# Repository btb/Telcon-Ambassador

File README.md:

# Telcon Ambassador Portable Terminals

The Telcon Ambassador was a series of portable terminals by Telcon Industries (who later created the Zorba portable computer).

The info here is primarily derived from my reverse-engineering of a Telcon Ambassador IV which I acquired in very rough shape.

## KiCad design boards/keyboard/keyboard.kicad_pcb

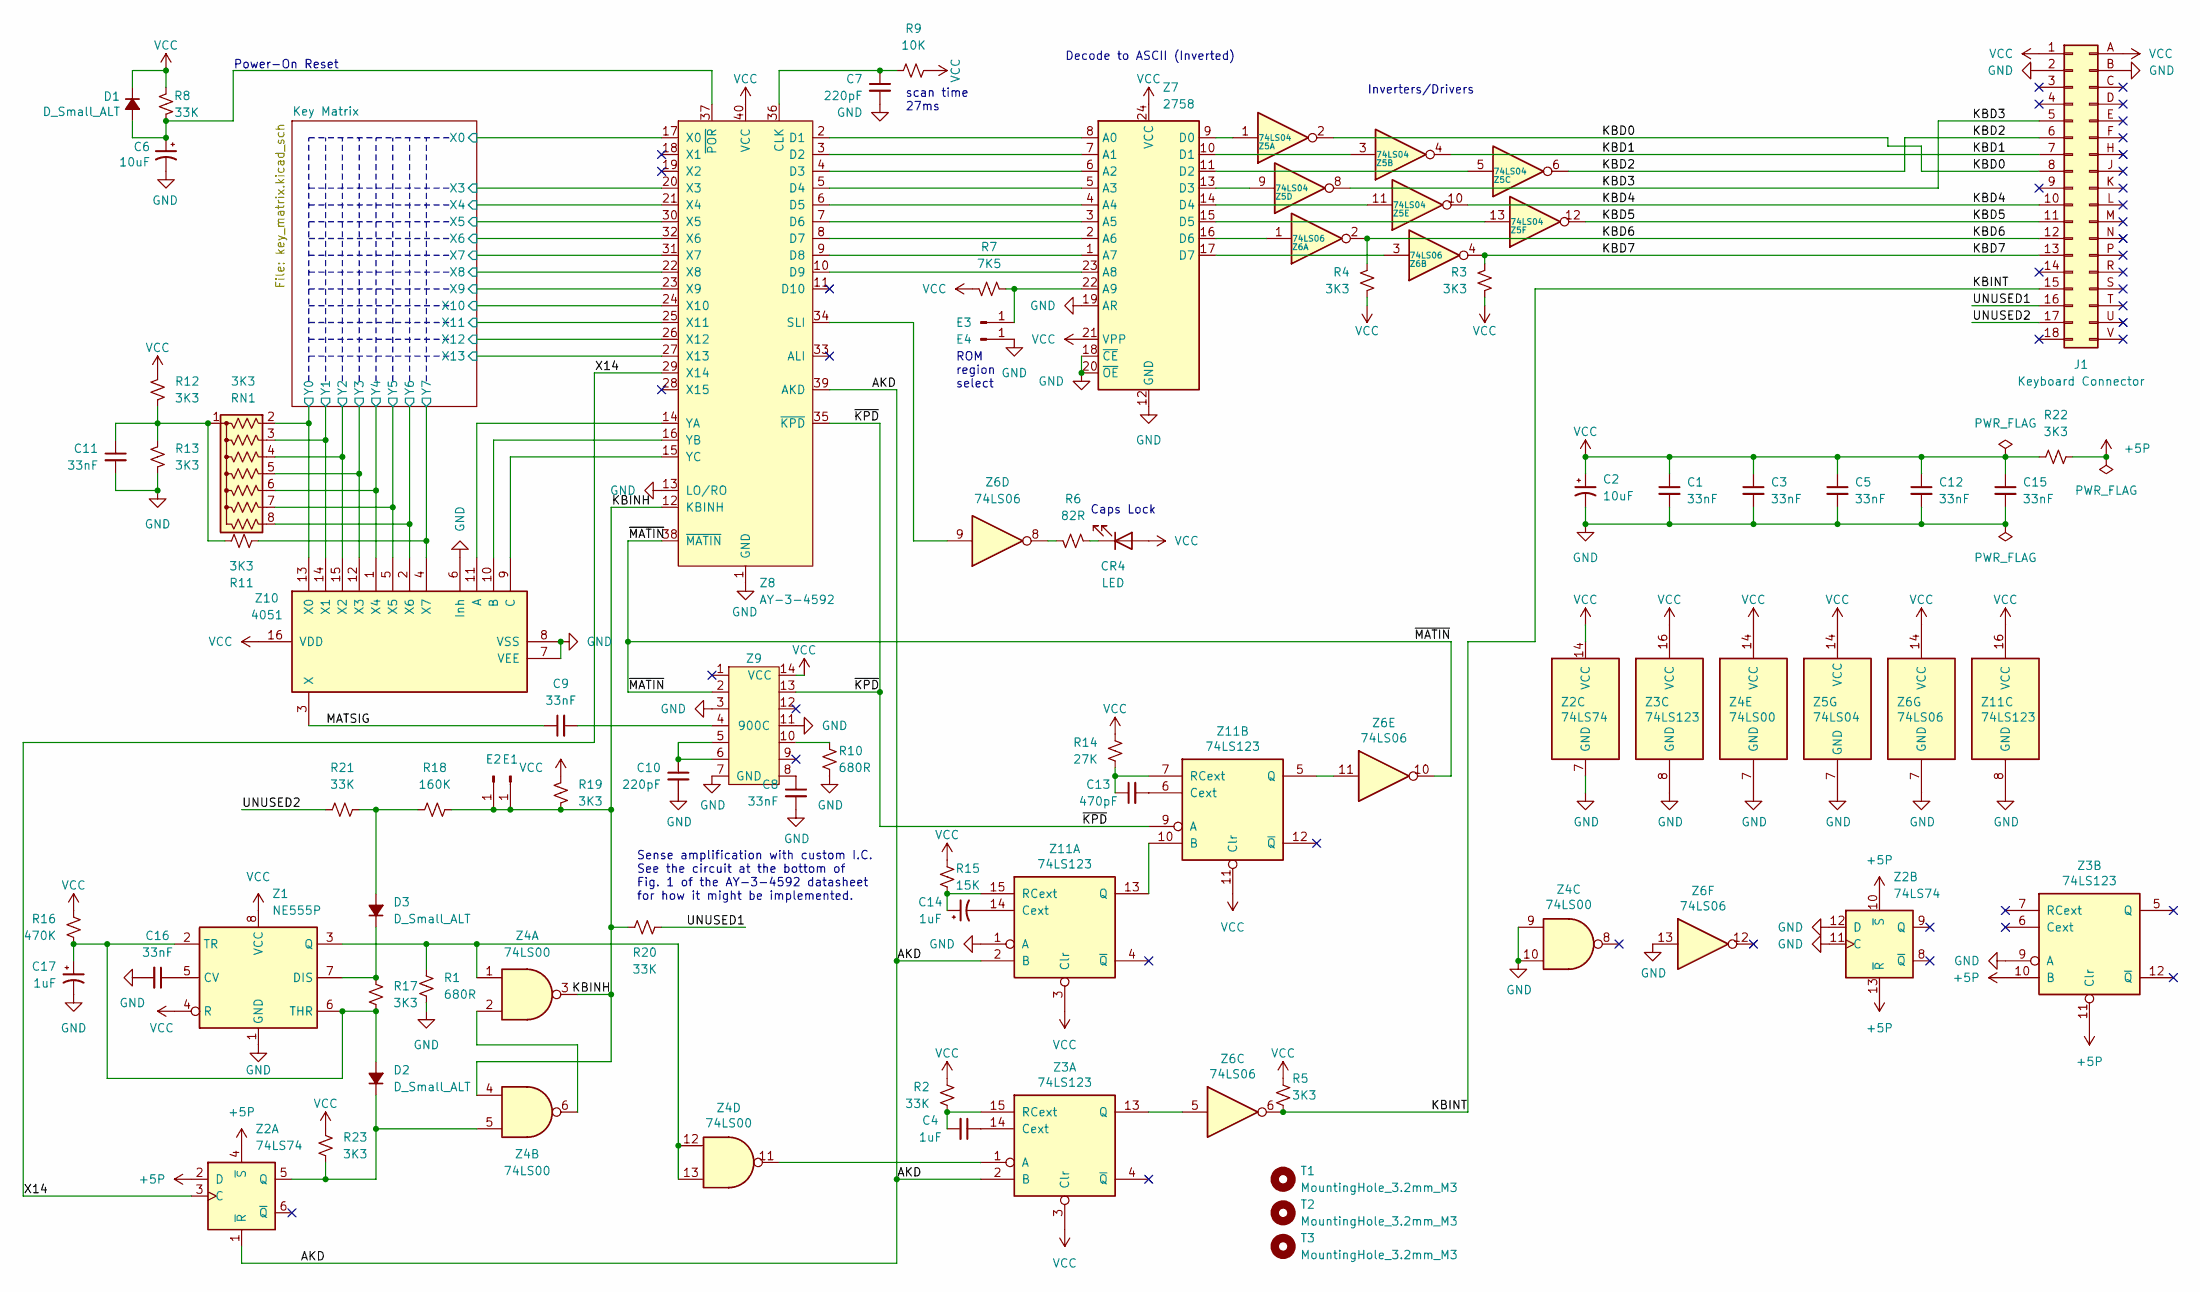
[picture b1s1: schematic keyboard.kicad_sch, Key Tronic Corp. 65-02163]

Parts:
C1, C3, C5, C8, C9, C11, C12, C15, C16: 33nF; C_Axial_L3.8mm_D2.6mm_P12.7mm_Horizontal
C2: 10uF; CP_Radial_D8.0mm_P3.80mm
C4: 1uF; C_Rect_L7.0mm_W2.5mm_P5.00mm
C6: 10uF; CP_Radial_D8.0mm_P3.50mm
C7, C10: 220pF; C_Disc_D6.0mm_W2.5mm_P6.35mm
C13: 470pF; C_Axial_L3.8mm_D2.6mm_P12.7mm_Horizontal
C14: 1uF; CP_Axial_L11.0mm_D5.0mm_P18.00mm_Horizontal
C17: 1uF; CP_Axial_L9.0mm_D3.5mm_P12.7mm_Horizontal
CR4: LED; LED_D5.0mm
D1, D2, D3: D_Small_ALT; D_T-1_P12.70mm_Horizontal
E1, E2: Conn_01x01_Male; PinHeader_1x01_P2.54mm_Vertical
E3: A9; PinHeader_1x01_P2.54mm_Vertical
E4: GND; PinHeader_1x01_P2.54mm_Vertical
J1: Keyboard Connector; CARDEDGE_2x18_P3.96mm
R1, R10: 680R; R_Axial_DIN0309_L9.0mm_D3.2mm_P12.70mm_Horizontal
R2, R8, R20, R21: 33K; R_Axial_DIN0309_L9.0mm_D3.2mm_P12.70mm_Horizontal
R3, R4, R5, R11, R12, R13, R17, R19, R22, R23: 3K3; R_Axial_DIN0309_L9.0mm_D3.2mm_P12.70mm_Horizontal
R6: 82R; R_Axial_DIN0309_L9.0mm_D3.2mm_P12.70mm_Horizontal
R7: 7K5; R_Axial_DIN0309_L9.0mm_D3.2mm_P12.70mm_Horizontal
R9: 10K; R_Axial_DIN0309_L9.0mm_D3.2mm_P12.70mm_Horizontal
R14: 27K; R_Axial_DIN0309_L9.0mm_D3.2mm_P12.70mm_Horizontal
R15: 15K; R_Axial_DIN0309_L9.0mm_D3.2mm_P12.70mm_Horizontal
R16: 470K; R_Axial_DIN0309_L9.0mm_D3.2mm_P12.70mm_Horizontal
R18: 160K; R_Axial_DIN0309_L9.0mm_D3.2mm_P12.70mm_Horizontal
RN1: 3K3; R_Array_SIP8
T1, T2, T3: MountingHole_3.2mm_M3
Z1: NE555P; DIP-8_W7.62mm
Z2: 74LS74; DIP-14_W7.62mm
Z3, Z11: 74LS123; DIP-16_W7.62mm
Z4: 74LS00; DIP-14_W7.62mm
Z5: 74LS04; DIP-14_W7.62mm
Z6: 74LS06; DIP-14_W7.62mm
Z7: 2758; DIP-24_W15.24mm
Z8: AY-3-4592; DIP-40_W15.24mm_Socket
Z9: 900C; DIP-14_W7.62mm
Z10: 4051; DIP-16_W7.62mm

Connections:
+5P: R22.2, Z2.2 (D), Z2.4 (~S), Z2.10 (~S), Z2.13 (~R), Z3.10 (B), Z3.11 (Clr)
/AKD: Z2.1 (~R), Z3.2 (B), Z8.39 (AKD), Z11.2 (B)
/KBD0: J1.8, Z5.2
/KBD1: J1.7, Z5.4
/KBD2: J1.6, Z5.6
/KBD3: J1.5, Z5.8
/KBD4: J1.10, Z5.10
/KBD5: J1.11, Z5.12
/KBD6: J1.12, R4.2, Z6.2
/KBD7: J1.13, R3.2, Z6.4
/KBINH: E1.1, E2.1, R18.2, R19.2, R20.1, Z4.3, Z4.4, Z8.12 (KBINH)
/KBINT: J1.15, R5.2, Z6.6
/Key Matrix/X0: Z8.17 (X0); also elsewhere on the board
/Key Matrix/X3: Z8.20 (X3); also elsewhere on the board
/Key Matrix/X4: Z8.21 (X4); also elsewhere on the board
/Key Matrix/X5: Z8.30 (X5); also elsewhere on the board
/Key Matrix/X6: Z8.32 (X6); also elsewhere on the board
/Key Matrix/X7: Z8.31 (X7); also elsewhere on the board
/Key Matrix/X8: Z8.22 (X8); also elsewhere on the board
/Key Matrix/X9: Z8.23 (X9); also elsewhere on the board
/Key Matrix/X10: Z8.24 (X10); also elsewhere on the board
/Key Matrix/X11: Z8.25 (X11); also elsewhere on the board
/Key Matrix/X12: Z8.26 (X12); also elsewhere on the board
/Key Matrix/X13: Z8.27 (X13); also elsewhere on the board
/Key Matrix/Y0: RN1.2 (R1), Z10.13 (X0); also elsewhere on the board
/Key Matrix/Y1: RN1.3 (R2), Z10.14 (X1); also elsewhere on the board
/Key Matrix/Y2: RN1.4 (R3), Z10.15 (X2); also elsewhere on the board
/Key Matrix/Y3: RN1.5 (R4), Z10.12 (X3); also elsewhere on the board
/Key Matrix/Y4: RN1.6 (R5), Z10.1 (X4); also elsewhere on the board
/Key Matrix/Y5: RN1.7 (R6), Z10.5 (X5); also elsewhere on the board
/Key Matrix/Y6: RN1.8 (R7), Z10.2 (X6); also elsewhere on the board
/Key Matrix/Y7: R11.2, Z10.4 (X7); also elsewhere on the board
/MATSIG: C9.1, Z10.3 (X)
/UNUSED1: J1.16, R20.2
/UNUSED2: J1.17, R21.2
/X14: Z2.3 (C), Z8.29 (X14)
/~KPD: Z8.35 (~KPD), Z9.13, Z11.9 (A)
/~MATIN: Z6.10, Z8.38 (~MATIN), Z9.2
GND: C1.2, C2.2, C3.2, C5.2, C6.2, C7.2, C8.2, C10.2, C11.2, C12.2, C15.2, C16.2, C17.2, E4.1, J1.2, J1.B, R1.2, R10.2, R13.2, Z1.1 (GND), Z2.7 (GND), Z2.11 (C), Z2.12 (D), Z3.8 (GND), Z3.9 (A), Z4.7 (GND), Z4.9, Z4.10, Z5.7 (GND), Z6.7 (GND), Z6.13, Z7.12 (GND), Z7.18 (~CE), Z7.19 (AR), Z7.20 (~OE), Z8.1 (GND), Z8.13 (LO/RO), Z9.3, Z9.7 (GND), Z9.11, Z10.6 (Inh), Z10.7 (VEE), Z10.8 (VSS), Z11.1 (A), Z11.8 (GND); also elsewhere on the board
unnamed: C4.1, Z3.14 (Cext)
unnamed: C4.2, R2.2, Z3.15 (RCext)
unnamed: C6.1, D1.2 (A), R8.2, Z8.37 (~POR)
unnamed: C7.1, R9.2, Z8.36 (CLK)
unnamed: C8.1, Z9.8
unnamed: C9.2, Z9.4
unnamed: C10.1, Z9.5, Z9.6
unnamed: C11.1, R11.1, R12.2, R13.1, RN1.1 (common)
unnamed: C13.1, R14.2, Z11.7 (RCext)
unnamed: C13.2, Z11.6 (Cext)
unnamed: C14.1, R15.2, Z11.15 (RCext)
unnamed: C14.2, Z11.14 (Cext)
unnamed: C16.1, Z1.5 (CV)
unnamed: C17.1, D2.2 (A), R16.2, R17.2, Z1.2 (TR), Z1.6 (THR)
unnamed: CR4.1 (K), R6.1
unnamed: D2.1 (K), R23.2, Z2.5 (Q), Z4.5
unnamed: D3.1 (K), R17.1, Z1.7 (DIS)
unnamed: D3.2 (A), R18.1, R21.1
unnamed: E3.1, R7.2, Z7.22 (A9)
unnamed: R1.1, Z1.3 (Q), Z4.1, Z4.12, Z4.13
unnamed: R6.2, Z6.8
unnamed: R10.1, Z9.10
unnamed: Z3.1 (A), Z4.11
unnamed: Z3.13 (Q), Z6.5
unnamed: Z4.2, Z4.6
unnamed: Z5.1, Z7.9 (D0)
unnamed: Z5.3, Z7.10 (D1)
unnamed: Z5.5, Z7.11 (D2)
unnamed: Z5.9, Z7.13 (D3)
unnamed: Z5.11, Z7.14 (D4)
unnamed: Z5.13, Z7.15 (D5)
unnamed: Z6.1, Z7.16 (D6)
unnamed: Z6.3, Z7.17 (D7)
unnamed: Z6.9, Z8.34 (SLI)
unnamed: Z7.1 (A7), Z8.9 (D8)
unnamed: Z7.2 (A6), Z8.8 (D7)
unnamed: Z7.3 (A5), Z8.7 (D6)
unnamed: Z7.4 (A4), Z8.6 (D5)
unnamed: Z7.5 (A3), Z8.5 (D4)
unnamed: Z7.6 (A2), Z8.4 (D3)
unnamed: Z7.7 (A1), Z8.3 (D2)
unnamed: Z7.8 (A0), Z8.2 (D1)
unnamed: Z7.23 (A8), Z8.10 (D9)
unnamed: Z8.15 (YC), Z10.9 (C)
unnamed: Z8.16 (YB), Z10.10 (B)
unnamed: Z8.14 (YA), Z10.11 (A)
unnamed: Z6.11, Z11.5 (Q)
unnamed: Z11.10 (B), Z11.13 (Q)
VCC: C1.1, C2.1, C3.1, C5.1, C12.1, C15.1, CR4.2 (A), D1.1 (K), J1.1, J1.A, R2.1, R3.1, R4.1, R5.1, R7.1, R8.1, R9.1, R12.1, R14.1, R15.1, R16.1, R19.1, R22.1, R23.1, Z1.4 (R), Z1.8 (VCC), Z2.14 (VCC), Z3.3 (Clr), Z3.16 (VCC), Z4.14 (VCC), Z5.14 (VCC), Z6.14 (VCC), Z7.21 (VPP), Z7.24 (VCC), Z8.40 (VCC), Z9.14 (VCC), Z10.16 (VDD), Z11.3 (Clr), Z11.11 (Clr), Z11.16 (VCC)

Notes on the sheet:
Sense amplification with custom I.C. See the circuit at the bottom of Fig. 1 of the AY-3-4592 datasheet for how it might be implemented.
ROM region select
Caps Lock
Power-On Reset
Inverters/Drivers
Decode to ASCII (Inverted)
scan time 27ms

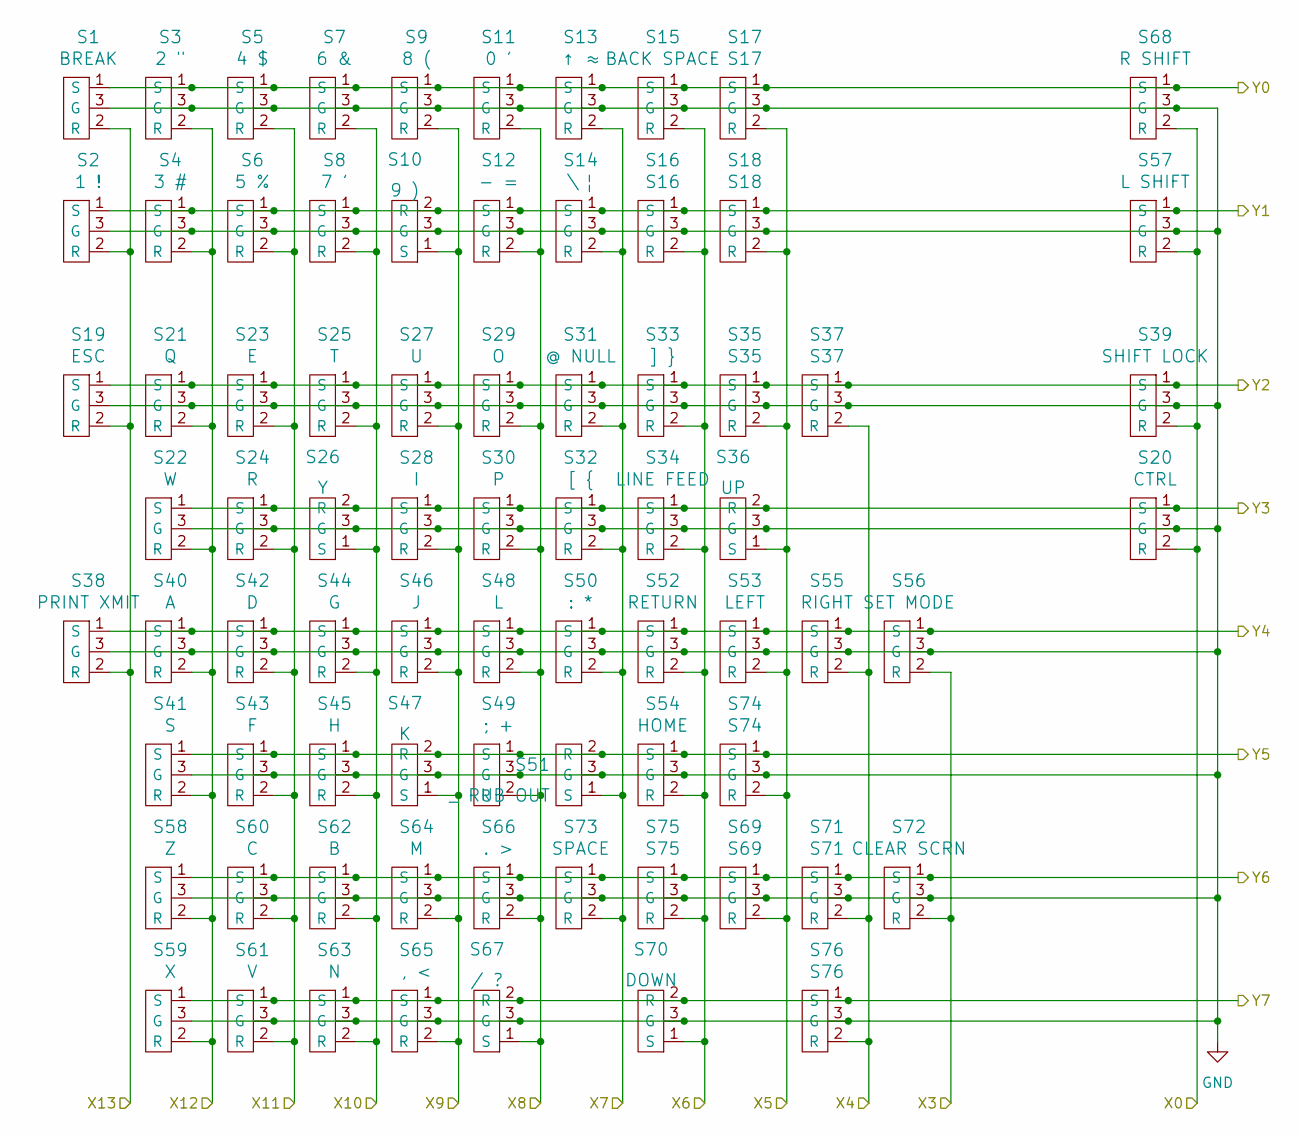
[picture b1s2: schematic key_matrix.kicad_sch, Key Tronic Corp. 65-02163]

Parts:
S1: BREAK; KTCPadScrew
S2: 1 !; KTCPad
S3: 2 "; KTCPad
S4: 3 #; KTCPad
S5: 4 $; KTCPadScrew
S6: 5 %; KTCPad
S7: 6 &; KTCPad
S8: 7 ’; KTCPad
S9: 8 (; KTCPad
S10: 9 ); KTCPadScrew
S11: 0 '; KTCPad
S12: - =; KTCPad
S13: ↑ ≈; KTCPad
S14: \ ¦; KTCPad
S15: BACK SPACE; KTCPadScrew
S16: S16; KTCPad
S17: S17; KTCPad
S18: S18; KTCPad
S19: ESC; KTCPad
S20: CTRL; KTCPad
S21: Q; KTCPadScrew
S22: W; KTCPad
S23: E; KTCPad
S24: R; KTCPad
S25: T; KTCPad
S26: Y; KTCPadScrew
S27: U; KTCPad
S28: I; KTCPad
S29: O; KTCPad
S30: P; KTCPad
S31: @ NULL; KTCPadScrew
S32: [ {; KTCPad
S33: ] }; KTCPad
S34: LINE FEED; KTCPad
S35: S35; KTCPad
S36: UP; KTCPadScrew
S37: S37; KTCPad
S38: PRINT XMIT; KTCPadScrew
S39: SHIFT LOCK; KTCPad
S40: A; KTCPad
S41: S; KTCPad
S42: D; KTCPadScrew
S43: F; KTCPad
S44: G; KTCPad
S45: H; KTCPad
S46: J; KTCPad
S47: K; KTCPadScrew
S48: L; KTCPad
S49: ; +; KTCPad
S50: : *; KTCPad
S51: _ RUB OUT; KTCPadScrew
S52: RETURN; KTCPad
S53: LEFT; KTCPadScrew
S54: HOME; KTCPad
S55: RIGHT; KTCPadScrew
S56: SET MODE; KTCPad
S57: L SHIFT; KTCPadScrew
S58: Z; KTCPad
S59: X; KTCPad
S60: C; KTCPad
S61: V; KTCPad
S62: B; KTCPadScrew
S63: N; KTCPad
S64: M; KTCPad
S65: , <; KTCPad
S66: . >; KTCPad
S67: / ?; KTCPadScrew
S68: R SHIFT; KTCPad
S69: S69; KTCPad
S70: DOWN; KTCPadScrew
S71: S71; KTCPad
S72: CLEAR SCRN; KTCPadScrew
S73: SPACE; KTCPadScrew
S74: S74; KTCPad
S75: S75; KTCPad
S76: S76; KTCPad

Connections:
/Key Matrix/X0: S20.2 (R), S39.2 (R), S57.2 (R), S68.2 (R); also elsewhere on the board
/Key Matrix/X3: S56.2 (R), S72.2 (R); also elsewhere on the board
/Key Matrix/X4: S37.2 (R), S55.2 (R), S71.2 (R), S76.2 (R); also elsewhere on the board
/Key Matrix/X5: S17.2 (R), S18.2 (R), S35.2 (R), S36.1 (S), S53.2 (R), S69.2 (R), S74.2 (R); also elsewhere on the board
/Key Matrix/X6: S15.2 (R), S16.2 (R), S33.2 (R), S34.2 (R), S52.2 (R), S54.2 (R), S70.1 (S), S75.2 (R); also elsewhere on the board
/Key Matrix/X7: S13.2 (R), S14.2 (R), S31.2 (R), S32.2 (R), S50.2 (R), S51.1 (S), S73.2 (R); also elsewhere on the board
/Key Matrix/X8: S11.2 (R), S12.2 (R), S29.2 (R), S30.2 (R), S48.2 (R), S49.2 (R), S66.2 (R), S67.1 (S); also elsewhere on the board
/Key Matrix/X9: S9.2 (R), S10.1 (S), S27.2 (R), S28.2 (R), S46.2 (R), S47.1 (S), S64.2 (R), S65.2 (R); also elsewhere on the board
/Key Matrix/X10: S7.2 (R), S8.2 (R), S25.2 (R), S26.1 (S), S44.2 (R), S45.2 (R), S62.2 (R), S63.2 (R); also elsewhere on the board
/Key Matrix/X11: S5.2 (R), S6.2 (R), S23.2 (R), S24.2 (R), S42.2 (R), S43.2 (R), S60.2 (R), S61.2 (R); also elsewhere on the board
/Key Matrix/X12: S3.2 (R), S4.2 (R), S21.2 (R), S22.2 (R), S40.2 (R), S41.2 (R), S58.2 (R), S59.2 (R); also elsewhere on the board
/Key Matrix/X13: S1.2 (R), S2.2 (R), S19.2 (R), S38.2 (R); also elsewhere on the board
/Key Matrix/Y0: S1.1 (S), S3.1 (S), S5.1 (S), S7.1 (S), S9.1 (S), S11.1 (S), S13.1 (S), S15.1 (S), S17.1 (S), S68.1 (S); also elsewhere on the board
/Key Matrix/Y1: S2.1 (S), S4.1 (S), S6.1 (S), S8.1 (S), S10.2 (R), S12.1 (S), S14.1 (S), S16.1 (S), S18.1 (S), S57.1 (S); also elsewhere on the board
/Key Matrix/Y2: S19.1 (S), S21.1 (S), S23.1 (S), S25.1 (S), S27.1 (S), S29.1 (S), S31.1 (S), S33.1 (S), S35.1 (S), S37.1 (S), S39.1 (S); also elsewhere on the board
/Key Matrix/Y3: S20.1 (S), S22.1 (S), S24.1 (S), S26.2 (R), S28.1 (S), S30.1 (S), S32.1 (S), S34.1 (S), S36.2 (R); also elsewhere on the board
/Key Matrix/Y4: S38.1 (S), S40.1 (S), S42.1 (S), S44.1 (S), S46.1 (S), S48.1 (S), S50.1 (S), S52.1 (S), S53.1 (S), S55.1 (S), S56.1 (S); also elsewhere on the board
/Key Matrix/Y5: S41.1 (S), S43.1 (S), S45.1 (S), S47.2 (R), S49.1 (S), S51.2 (R), S54.1 (S), S74.1 (S); also elsewhere on the board
/Key Matrix/Y6: S58.1 (S), S60.1 (S), S62.1 (S), S64.1 (S), S66.1 (S), S69.1 (S), S71.1 (S), S72.1 (S), S73.1 (S), S75.1 (S); also elsewhere on the board
/Key Matrix/Y7: S59.1 (S), S61.1 (S), S63.1 (S), S65.1 (S), S67.2 (R), S70.2 (R), S76.1 (S); also elsewhere on the board
GND: S1.3 (G), S2.3 (G), S3.3 (G), S4.3 (G), S5.3 (G), S6.3 (G), S7.3 (G), S8.3 (G), S9.3 (G), S10.3 (G), S11.3 (G), S12.3 (G), S13.3 (G), S14.3 (G), S15.3 (G), S16.3 (G), S17.3 (G), S18.3 (G), S19.3 (G), S20.3 (G), S21.3 (G), S22.3 (G), S23.3 (G), S24.3 (G), S25.3 (G), S26.3 (G), S27.3 (G), S28.3 (G), S29.3 (G), S30.3 (G), S31.3 (G), S32.3 (G), S33.3 (G), S34.3 (G), S35.3 (G), S36.3 (G), S37.3 (G), S38.3 (G), S39.3 (G), S40.3 (G), S41.3 (G), S42.3 (G), S43.3 (G), S44.3 (G), S45.3 (G), S46.3 (G), S47.3 (G), S48.3 (G), S49.3 (G), S50.3 (G), S51.3 (G), S52.3 (G), S53.3 (G), S54.3 (G), S55.3 (G), S56.3 (G), S57.3 (G), S58.3 (G), S59.3 (G), S60.3 (G), S61.3 (G), S62.3 (G), S63.3 (G), S64.3 (G), S65.3 (G), S66.3 (G), S67.3 (G), S68.3 (G), S69.3 (G), S70.3 (G), S71.3 (G), S72.3 (G), S73.3 (G), S74.3 (G), S75.3 (G), S76.3 (G); also elsewhere on the board

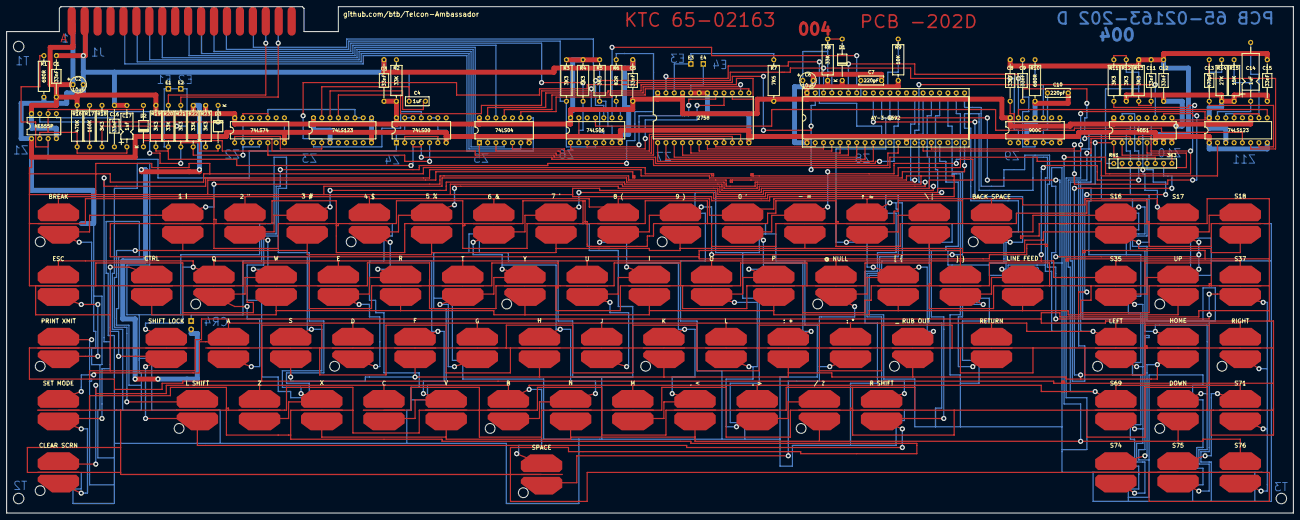
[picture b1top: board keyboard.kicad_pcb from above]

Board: 2 copper layers, 394.1 x 155.1 mm, 140 parts (0 on the bottom side), 88 nets.

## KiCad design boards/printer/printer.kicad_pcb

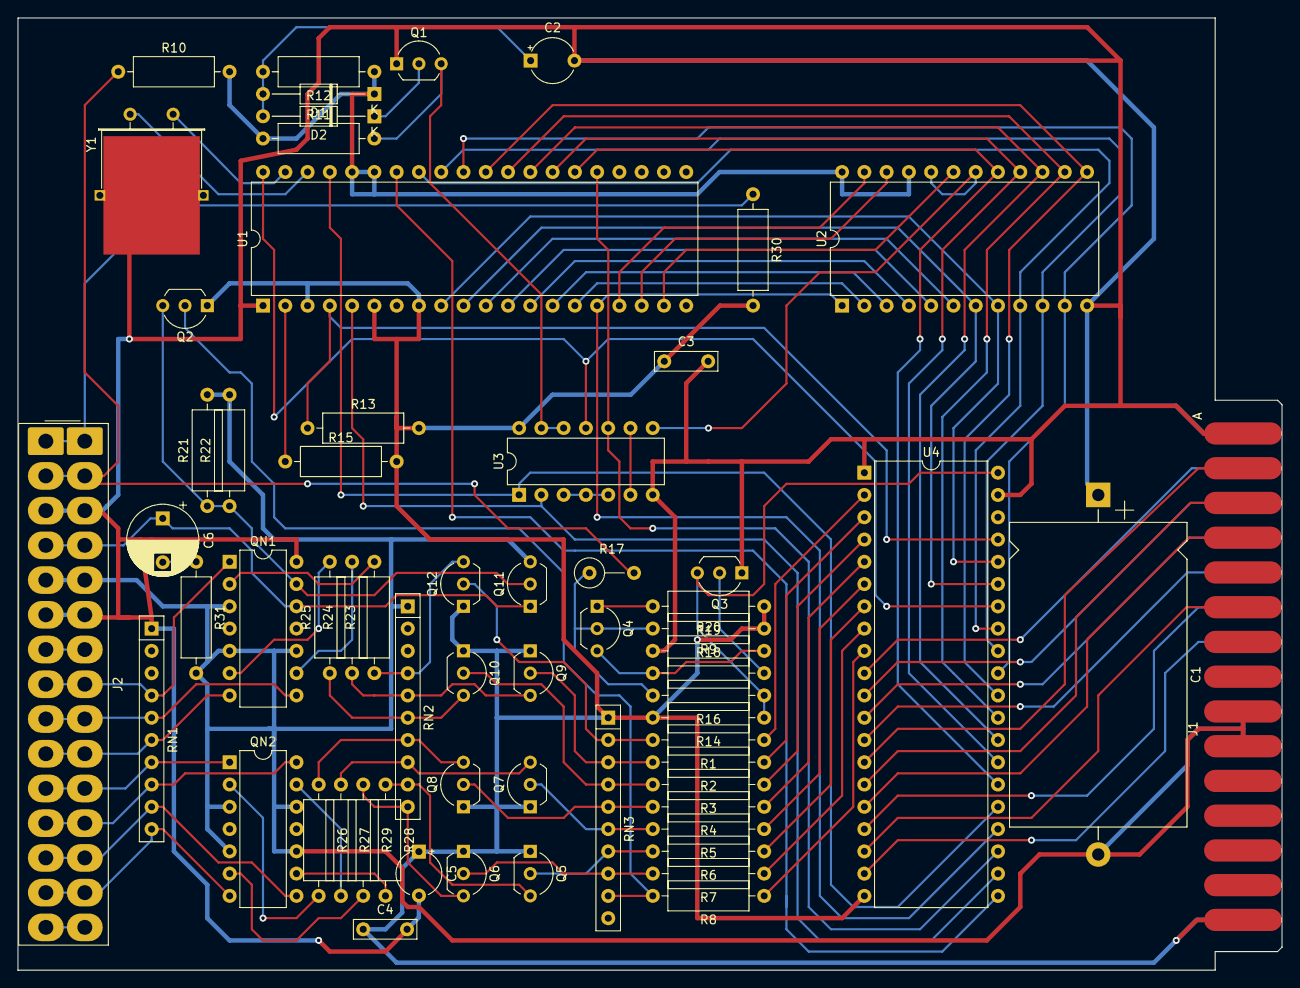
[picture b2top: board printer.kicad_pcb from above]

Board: 2 copper layers, 144.1 x 108.6 mm, 63 parts (0 on the bottom side), 95 nets.

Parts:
C1: 220uF; CP_Axial_L34.5mm_D20.0mm_P41.00mm_Horizontal
C2: 10UF; CP_Radial_Tantal_D5.0mm_P5.00mm
C3, C4: 220NF; C_Rect_L7.0mm_W2.0mm_P5.00mm
C5: 16uF; CP_Radial_Tantal_D5.0mm_P5.00mm
C6: 220uF; CP_Radial_D8.0mm_P5.00mm
D1, D2: 1N4148; D_DO-35_SOD27_P12.70mm_Horizontal
J1: GC-880; CARDEDGE_2x15_P3.96mm
J2: PRINTER; CardSocket_1x15_P3.96mm_Vertical
Q1, Q3: 2N3904; TO-92_Inline_Wide
Q2, Q4, Q5, Q6, Q7, Q8, Q9, Q10, Q11, Q12: 2N3906; TO-92_Inline_Wide
QN1, QN2: Q2T3725; DIP-14_W7.62mm
R1, R2, R3, R4, R5, R6, R7, R8, R9, R20: 10K; R_Axial_DIN0309_L9.0mm_D3.2mm_P12.70mm_Horizontal
R10: 2.2K; R_Axial_DIN0309_L9.0mm_D3.2mm_P12.70mm_Horizontal
R11: 27K; R_Axial_DIN0309_L9.0mm_D3.2mm_P12.70mm_Horizontal
R12: 47K; R_Axial_DIN0309_L9.0mm_D3.2mm_P12.70mm_Horizontal
R13, R14: 3.9K; R_Axial_DIN0309_L9.0mm_D3.2mm_P12.70mm_Horizontal
R15: 2.7K; R_Axial_DIN0309_L9.0mm_D3.2mm_P12.70mm_Horizontal
R16: 180K; R_Axial_DIN0309_L9.0mm_D3.2mm_P12.70mm_Horizontal
R17: 2.7K; R_Axial_DIN0309_L9.0mm_D3.2mm_P5.08mm_Vertical
R18: 220K; R_Axial_DIN0309_L9.0mm_D3.2mm_P12.70mm_Horizontal
R19: 1K; R_Axial_DIN0309_L9.0mm_D3.2mm_P12.70mm_Horizontal
R21, R22: 5.6K; R_Axial_DIN0309_L9.0mm_D3.2mm_P12.70mm_Horizontal
R23, R24, R25, R26, R27, R28, R29: 1k; R_Axial_DIN0309_L9.0mm_D3.2mm_P12.70mm_Horizontal
R30: 150; R_Axial_DIN0309_L9.0mm_D3.2mm_P12.70mm_Horizontal
R31: 100; R_Axial_DIN0309_L9.0mm_D3.2mm_P12.70mm_Horizontal
RN1, RN2: 10K; R_Array_SIP10
RN3: 2.7K; R_Array_SIP10
U1: MC6802; DIP-40_W15.24mm
U2: 2758; DIP-24_W15.24mm
U3: 7400; DIP-14_W7.62mm
U4: 6821; DIP-40_W15.24mm
Y1: Crystal_GND3; Crystal_HC18-U_Horizontal_1EP_style2

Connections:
-24V: C1.2, J1.9, J1.10, J1.K, J1.L, J2.5, J2.E, Q11.3 (C), QN1.3 (E), QN1.5 (E), QN1.10 (E), QN2.3 (E), QN2.5 (E), QN2.10 (E), QN2.12 (E), R21.2, R22.2, R31.2, RN2.1 (R1.1)
/A0: U1.9 (A0), U2.8 (A0), U4.36 (RS0)
/A1: U1.10 (A1), U2.7 (A1), U4.35 (RS1)
/A2: U1.11 (A2), U2.6 (A2)
/A3: U1.12 (A3), U2.5 (A3)
/A4: U1.13 (A4), U2.4 (A4)
/A5: U1.14 (A5), U2.3 (A5)
/A6: U1.15 (A6), U2.2 (A6)
/A7: U1.16 (A7), U2.1 (A7), U4.24 (CS1)
/A8: U1.17 (A8), U2.23 (A8)
/A9: U1.18 (A9), U2.22 (A9)
/A10: U1.19 (A10), U2.19 (AR)
/A15: U1.25 (A15), U3.10, U4.23 (~CS2)
/D0: U1.33 (D0), U2.9 (D0), U4.33 (D0)
/D1: U1.32 (D1), U2.10 (D1), U4.32 (D1)
/D2: U1.31 (D2), U2.11 (D2), U4.31 (D2)
/D3: U1.30 (D3), U2.13 (D3), U4.30 (D3)
/D4: U1.29 (D4), U2.14 (D4), U4.29 (D4)
/D5: U1.28 (D5), U2.15 (D5), U4.28 (D5)
/D6: U1.27 (D6), U2.16 (D6), U4.27 (D6)
/D7: U1.26 (D7), U2.17 (D7), U4.26 (D7)
/ENABLE: U1.37 (E), U3.1, U4.25 (ENABLE)
/HEAD1: J2.8, J2.J, QN1.1 (C), RN1.4 (R3)
/HEAD2: J2.9, J2.K, QN1.8 (C), RN1.5 (R4)
/HEAD3: J2.10, J2.L, QN1.7 (C), RN1.6 (R5)
/HEAD4: J2.11, J2.M, QN2.1 (C), RN1.7 (R6)
/HEAD5: J2.12, J2.N, QN2.14 (C), RN1.8 (R7)
/HEAD6: J2.13, J2.P, QN2.8 (C), RN1.9 (R8)
/HEAD7: J2.14, J2.R, QN2.7 (C), RN1.10 (R9)
/IRQ: R13.1, U1.4 (~IRQ), U4.37 (~IRQB), U4.38 (~IRQA)
/MOTOR: C6.1, J2.4, J2.D, Q11.1 (E), QN1.12 (E)
/PHOTOTRANSISTOR: J2.2, J2.B, R10.1, R17.2
/PRCON: J1.7, U4.19 (CB2)
/PRD0: J1.2, U4.10 (PB0)
/PRD1: J1.3, U4.11 (PB1)
/PRD2: J1.4, U4.12 (PB2)
/PRD3: J1.5, U4.13 (PB3)
/PRD4: J1.B, U4.14 (PB4)
/PRD5: J1.C, U4.15 (PB5)
/PRD6: J1.D, U4.16 (PB6)
/PRD7: J1.6, U4.17 (PB7)
/PRINT: J1.F, U4.18 (CB1)
/R/~W: U1.34 (R/~W), U4.21 (R/~W)
/VMA: U1.5 (VMA), U3.2, U4.22 (CS0)
/~RESET: U1.40 (~RESET), U3.11, U4.34 (~RESET)
GND: C1.1, C2.2, C3.2, C4.2, C5.2, J1.1, J1.A, J2.3, J2.6, J2.C, J2.F, Q1.1 (E), Q3.1 (E), QN1.14 (C), R20.1, RN1.1 (common), U1.1 (VSS), U2.12 (GND), U3.7 (GND), U4.1 (VSS), U4.39 (CA2), Y1.3
unnamed: C6.2, R31.1
unnamed: C2.1, D1.2 (A), D2.2 (A), R12.2
unnamed: D2.1 (K), Q1.2 (B)
unnamed: J2.1, J2.A, R30.1
unnamed: J2.7, J2.H
unnamed: J2.15, J2.S
unnamed: Q1.3 (C), R11.2, U3.12, U3.13
unnamed: Q2.2 (B), R8.2, RN3.9 (R8)
unnamed: Q3.2 (B), R9.2
unnamed: Q3.3 (C), R14.1, R16.1, U4.40 (CA1)
unnamed: Q4.2 (B), Q4.3 (C), R9.1, R16.2, R17.1, R18.2, R20.2
unnamed: Q4.1 (E), R19.2
unnamed: Q5.2 (B), R6.2, RN3.7 (R6)
unnamed: Q5.3 (C), R28.1, RN2.9 (R8.2)
unnamed: Q6.2 (B), R7.2, RN3.8 (R7)
unnamed: Q6.3 (C), R29.1, RN2.10 (R9.2)
unnamed: Q7.2 (B), R5.2, RN3.6 (R5)
unnamed: Q7.3 (C), R27.1, RN2.8 (R7.2)
unnamed: Q8.2 (B), R4.2, RN3.5 (R4)
unnamed: Q8.3 (C), R26.1, RN2.7 (R6.2)
unnamed: Q9.2 (B), R2.2, RN3.3 (R2)
unnamed: Q9.3 (C), R24.1, RN2.5 (R4.2)
unnamed: Q10.2 (B), R3.2, RN3.4 (R3)
unnamed: Q10.3 (C), R25.1, RN2.6 (R5.2)
unnamed: Q2.3 (C), Q11.2 (B), QN1.13 (B), R21.1, R22.1
unnamed: Q12.2 (B), R1.2, RN3.2 (R1)
unnamed: Q12.3 (C), R23.1, RN2.4 (R3.2)
unnamed: QN1.2 (B), R23.2
unnamed: QN1.6 (B), R25.2
unnamed: QN1.9 (B), R24.2
unnamed: QN2.2 (B), R26.2
unnamed: QN2.6 (B), R29.2
unnamed: QN2.9 (B), R28.2
unnamed: QN2.13 (B), R27.2
unnamed: U1.39 (EXTAL), Y1.2
unnamed: U1.38 (XTAL), Y1.1
unnamed: R15.1, U1.2 (~HALT)
unnamed: U2.18 (~CE), U2.20 (~OE), U3.8
unnamed: U3.3, U3.4, U3.5
unnamed: U3.6, U3.9
unnamed: R1.1, U4.2 (PA0)
unnamed: R2.1, U4.3 (PA1)
unnamed: R3.1, U4.4 (PA2)
unnamed: R4.1, U4.5 (PA3)
unnamed: R5.1, U4.6 (PA4)
unnamed: R6.1, U4.7 (PA5)
unnamed: R7.1, U4.8 (PA6)
unnamed: R8.1, U4.9 (PA7)
VCC: C3.1, C4.1, C5.1, D1.1 (K), J1.15, J1.S, Q2.1 (E), Q5.1 (E), Q6.1 (E), Q7.1 (E), Q8.1 (E), Q9.1 (E), Q10.1 (E), Q12.1 (E), R10.2, R11.1, R12.1, R13.2, R14.2, R15.2, R18.1, R19.1, R30.2, RN3.1 (common), U1.3 (MR), U1.6 (~NMI), U1.8 (VCC), U1.35 (VCC_STANDBY), U1.36 (RE), U2.21 (VPP), U2.24 (VCC), U3.14 (VCC), U4.20 (VCC)

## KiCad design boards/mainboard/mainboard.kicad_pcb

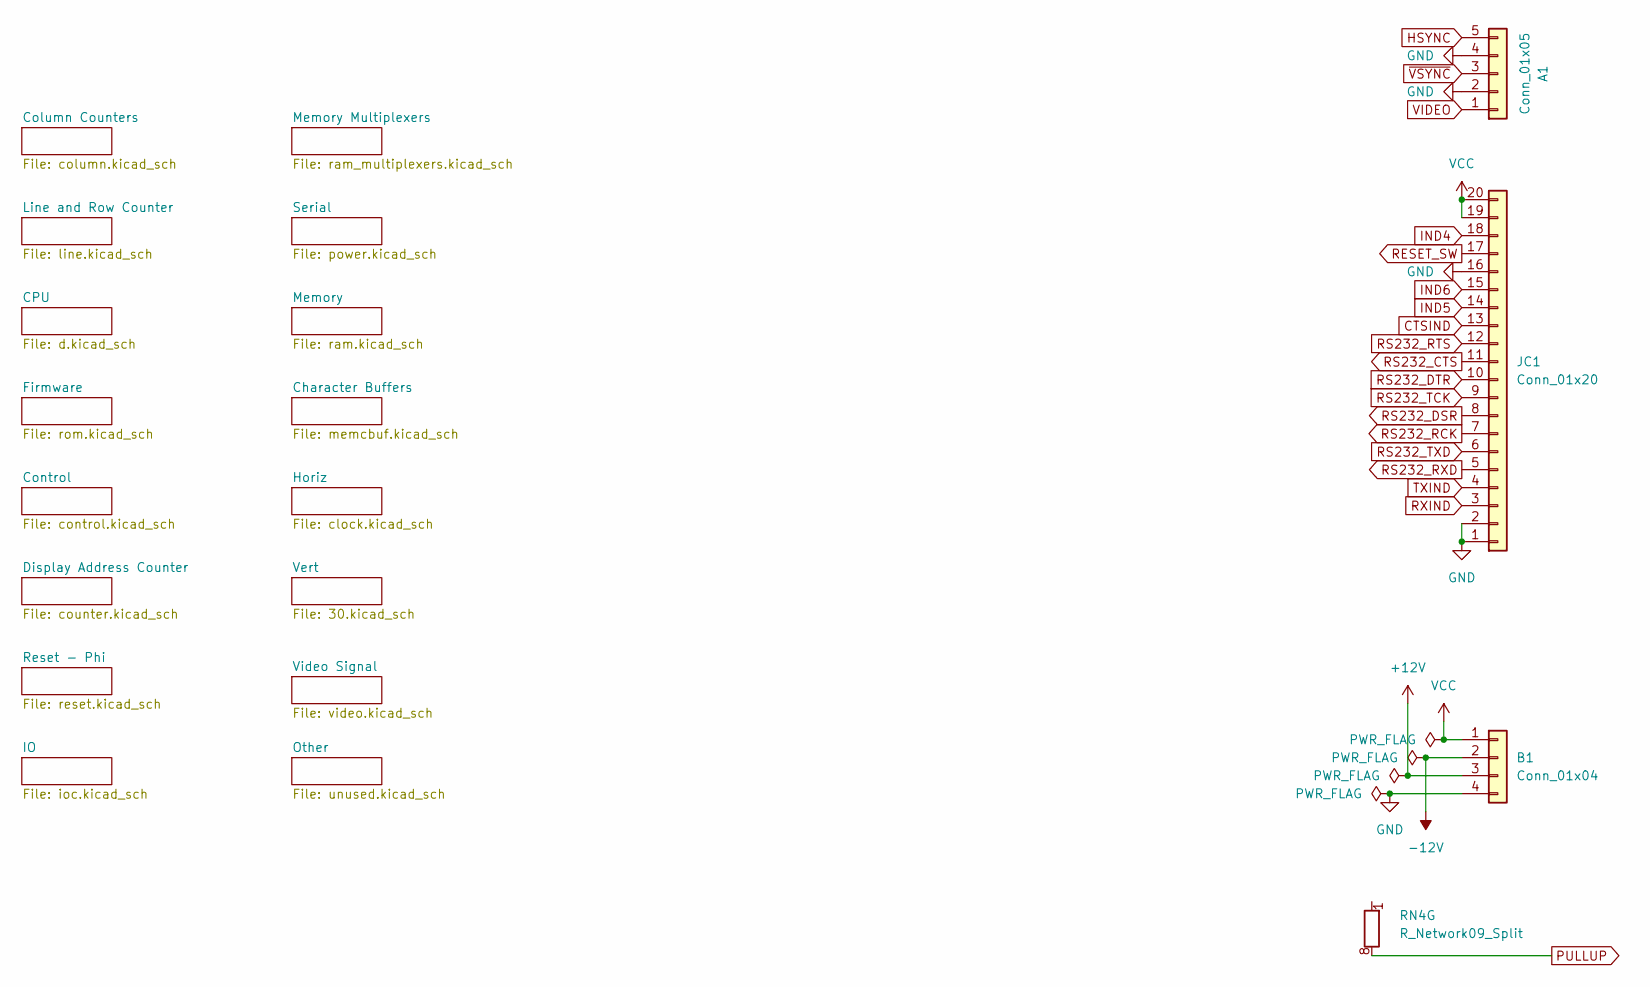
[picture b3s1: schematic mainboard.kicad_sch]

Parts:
A1: Conn_01x05; SolderWire-0.75sqmm_1x05_P6.35mm_D1.25mm_OD2.3mm
B1: Conn_01x04; SolderWire-2sqmm_1x04_P7.8mm_D2mm_OD3.9mm
JC1: Conn_01x20; SolderWire-0.75sqmm_1x020_P3.96mm_D1.25mm_OD2.3mm
RN4: R_Network09_Split; R_Array_SIP10

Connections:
+12V: B1.3; also elsewhere on the board
-12V: B1.2; also elsewhere on the board
CTSIND: JC1.13; also elsewhere on the board
GND: A1.2, A1.4, B1.4, JC1.1, JC1.2, JC1.16; also elsewhere on the board
HSYNC: A1.5; also elsewhere on the board
IND4: JC1.18; also elsewhere on the board
IND5: JC1.14; also elsewhere on the board
IND6: JC1.15; also elsewhere on the board
PULLUP: RN4.8 (R7.2); also elsewhere on the board
RESET_SW: JC1.17; also elsewhere on the board
RS232_CTS: JC1.11; also elsewhere on the board
RS232_DSR: JC1.8; also elsewhere on the board
RS232_DTR: JC1.10; also elsewhere on the board
RS232_RCK: JC1.7, JC1.9; also elsewhere on the board
RS232_RTS: JC1.12; also elsewhere on the board
RS232_RXD: JC1.5; also elsewhere on the board
RS232_TXD: JC1.6; also elsewhere on the board
RXIND: JC1.3; also elsewhere on the board
TXIND: JC1.4; also elsewhere on the board
VCC: B1.1, JC1.19, JC1.20; also elsewhere on the board
VIDEO: A1.1; also elsewhere on the board
~VSYNC: A1.3; also elsewhere on the board

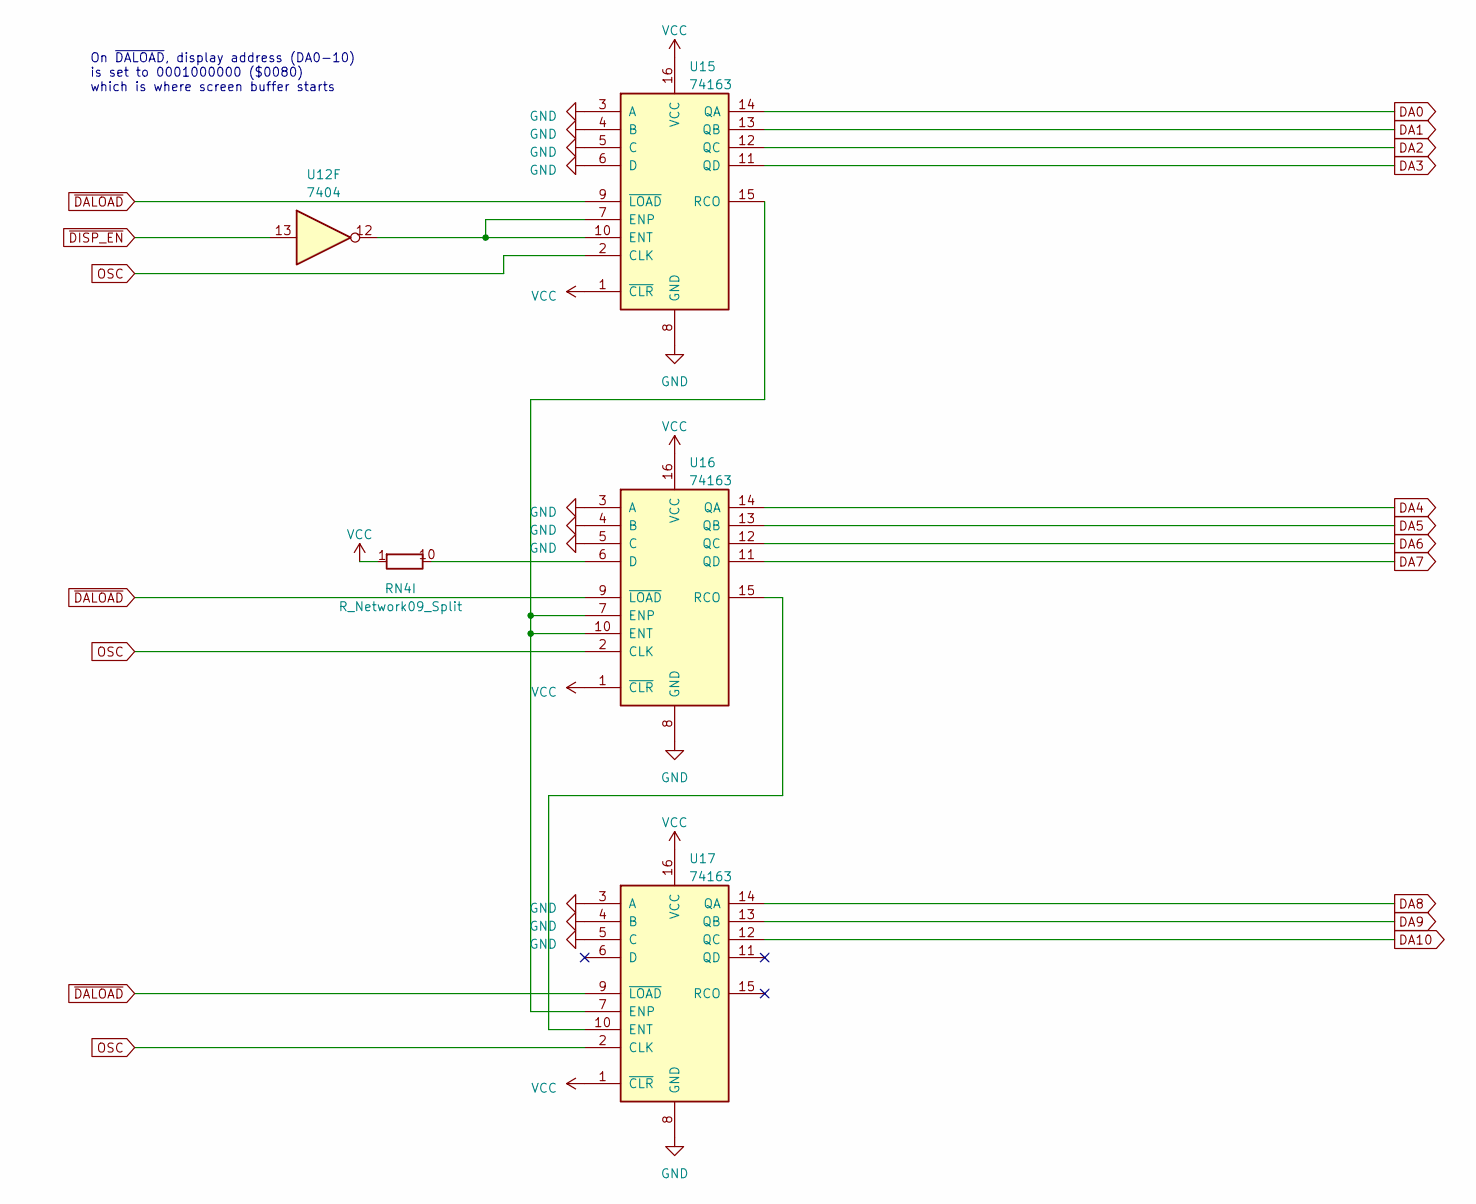
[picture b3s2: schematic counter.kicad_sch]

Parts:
RN4: R_Network09_Split; R_Array_SIP10
U12: 7404; DIP-14_W7.62mm
U15, U16, U17: 74163; DIP-16_W7.62mm

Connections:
DA0: U15.14 (QA); also elsewhere on the board
DA1: U15.13 (QB); also elsewhere on the board
DA2: U15.12 (QC); also elsewhere on the board
DA3: U15.11 (QD); also elsewhere on the board
DA4: U16.14 (QA); also elsewhere on the board
DA5: U16.13 (QB); also elsewhere on the board
DA6: U16.12 (QC); also elsewhere on the board
DA7: U16.11 (QD); also elsewhere on the board
DA8: U17.14 (QA); also elsewhere on the board
DA9: U17.13 (QB); also elsewhere on the board
DA10: U17.12 (QC); also elsewhere on the board
GND: U15.3 (A), U15.4 (B), U15.5 (C), U15.6 (D), U15.8 (GND), U16.3 (A), U16.4 (B), U16.5 (C), U16.8 (GND), U17.3 (A), U17.4 (B), U17.5 (C), U17.8 (GND); also elsewhere on the board
unnamed: RN4.10 (R9.2), U16.6 (D)
unnamed: U12.12, U15.7 (ENP), U15.10 (ENT)
unnamed: U15.15 (RCO), U16.7 (ENP), U16.10 (ENT), U17.7 (ENP)
unnamed: U16.15 (RCO), U17.10 (ENT)
OSC: U15.2 (CLK), U16.2 (CLK), U17.2 (CLK); also elsewhere on the board
VCC: U15.1 (~CLR), U15.16 (VCC), U16.1 (~CLR), U16.16 (VCC), U17.1 (~CLR), U17.16 (VCC); also elsewhere on the board
~DALOAD: U15.9 (~LOAD), U16.9 (~LOAD), U17.9 (~LOAD); also elsewhere on the board
~DISP_EN: U12.13; also elsewhere on the board

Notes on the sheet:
On ~{DALOAD}, display address (DA0-10) is set to 0001000000 ($0080) which is where screen buffer starts
